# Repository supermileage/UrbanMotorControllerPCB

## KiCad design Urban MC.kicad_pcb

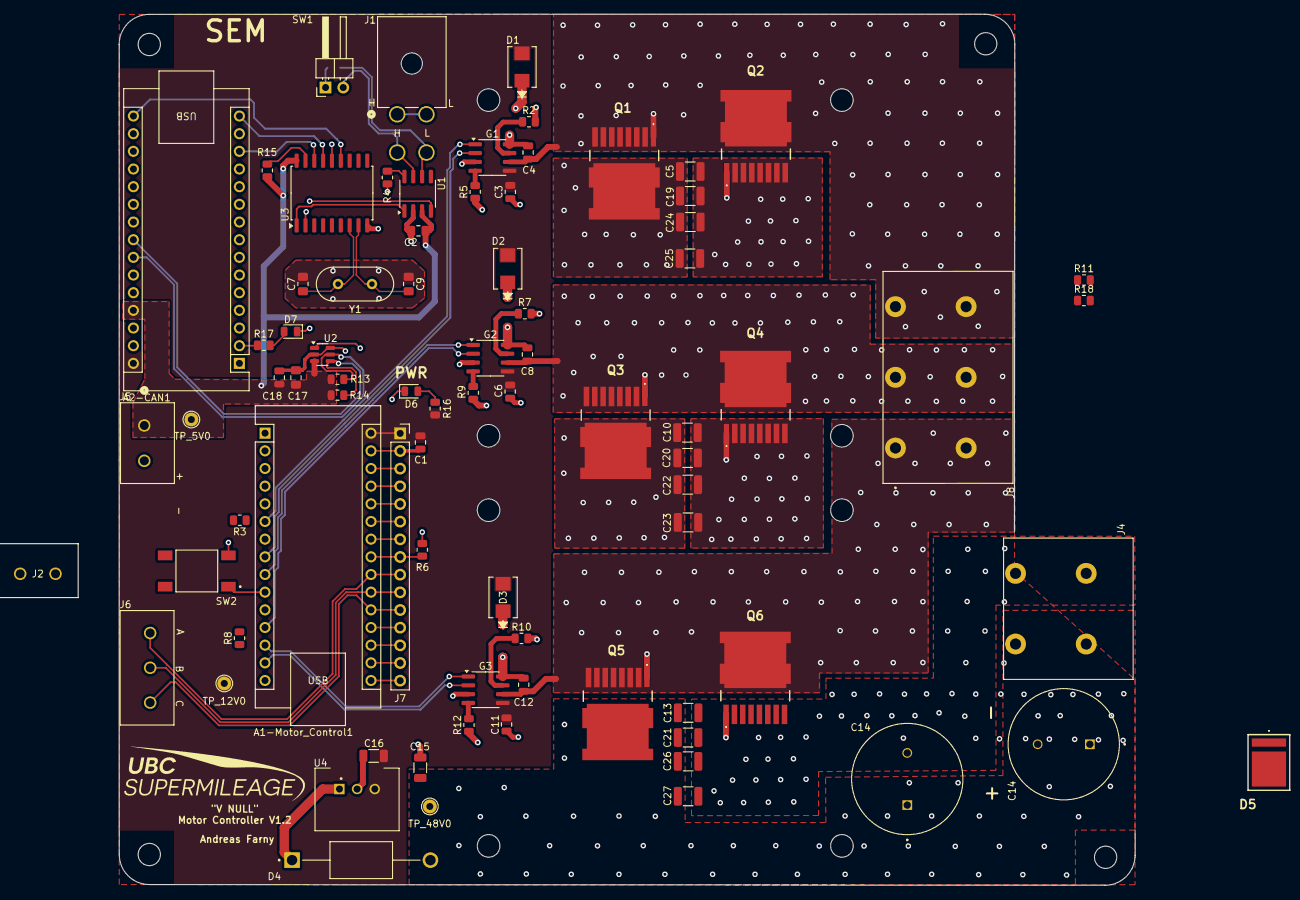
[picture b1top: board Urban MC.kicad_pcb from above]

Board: 6 copper layers, 146.1 x 125.2 mm, 83 parts (1 on the bottom side), 66 nets.

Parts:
A1-Motor_Control1, A2-CAN1: Arduino_Nano_v2.x; Arduino_Nano
C1, C3, C6, C8, C11, C12, C18: 10u; C_0805_2012Metric
C2, C17: 0.1uF; C_0805_2012Metric_Pad1.18x1.45mm_HandSolder
C4: 1u; C_0805_2012Metric
C5, C10, C13: 100 nF; C_1210_3225Metric
C7, C9: 16pF; C_0805_2012Metric_Pad1.18x1.45mm_HandSolder
C14, C14#2: 1m; CAPPRD750W80D1600H2500
C15: 1u; C_1206_3216Metric
C16: 22u; C_1206_3216Metric
C19, C20, C21: 1 uF; C_1210_3225Metric
C22, C24, C26: 4.7 uF; C_1210_3225Metric
C23, C25, C27: 10 uF; C_1210_3225Metric
D1, D2, D3: D; DIODE_DO214AA_MBRS_VIS
D4: D; DIOAD1990W125L900D530
D5: D_TVS; PTVS1058CH
D6, D7: LED; LED_0805_2012Metric
G1, G2, G3: IRS2186; SOIC-8_3.9x4.9mm_P1.27mm
HEATSINK: HEATSINK-518-95AB
HEATSINK#2: HEATSINK-518-95AB
J1: CAN; CONN_5569-04A_MOL
J2: UART_DYNO; CONN_OSTTC022162_OST
J4: VBAT; TE_1-1986660-2
J5: PWR_HALL; CONN_OSTTC022162_OST
J6: HALL_SENSORS; CONN_OSTTC030162_OST
J7: Conn_01x15_Socket; PinSocket_1x15_P2.54mm_Vertical
J8: Conn_02x03_CUSTOM; TE_1986660-3
Q1, Q2, Q3, Q4, Q5, Q6: NTBLS0D8N08XTXG; NVBLS1D1N08H
R1: 120; R_0805_2012Metric
R2, R5, R7, R9, R10, R12: 11Ω; R_0805_2012Metric
R3, R8, R11, R18: 0Ω; R_0805_2012Metric
R4, R15: 10k; R_0805_2012Metric
R6, R13, R14: 10K; R_0805_2012Metric
R16: 4.7k; R_0805_2012Metric
R17: 1.5k; R_0805_2012Metric
SW1: CAN_TERM; PinHeader_1x02_P2.54mm_Horizontal
SW2: SW_MEC_5E; SW_TS04-66-70-BK-160-SMT
TP_5V0, TP_12V0, TP_48V0: TestPoint; TestPoint_THTPad_D2.0mm_Drill1.0mm
U1: MCP2561/2; SOIC-8_3.9x4.9mm_P1.27mm
U2: MCP4725; SOT-23-6
U3: MCP2515-xSO; SOIC-18W_7.5x11.6mm_P1.27mm
U4: CONV_LCW78_12-1.0
Y1: 8MHz; Crystal_HC49-U_Vertical

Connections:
3.3V_OUT: A1-Motor_Control1.17 (3V3), J7.14
5V_OUT: A1-Motor_Control1.27 (+5V), J7.4
+5V: A2-CAN1.27 (+5V), C2.2, C17.1, C18.1, J5.1, R13.1, R14.1, R15.2, TP_5V0.1, U1.3 (VDD), U2.3 (VDD), U3.18 (VDD)
+12V: A1-Motor_Control1.30 (VIN), A2-CAN1.30 (VIN), C1.1, C3.2, C6.2, C11.2, C16.2, D1.2, D2.2, D3.2, G1.5 (VCC), G2.5 (VCC), G3.5 (VCC), J7.1, R16.1, TP_12V0.1, U4.3 (+VOUT)
+48V: C5.1, C10.1, C13.1, C14.1, C15.1, C19.1, C20.1, C21.1, C22.1, C23.1, C24.1, C25.1, C26.1, C27.1, D4.A, D5.2 (A2), J4.1_1 (Pin_1), J4.1_2 (Pin_2), Q1.9 (D), Q1.10 (D_2), Q1.11 (D_3), Q1.12 (D_4), Q3.9 (D), Q3.10 (D_2), Q3.11 (D_3), Q3.12 (D_4), Q5.9 (D), Q5.10 (D_2), Q5.11 (D_3), Q5.12 (D_4), TP_48V0.1
/A4: A2-CAN1.23 (A4), R14.2, U2.4 (SDA)
/A5: A2-CAN1.24 (A5), R13.2, U2.5 (SCL)
/CAN HIGH: J1.3, SW1.2, U1.7 (CANH)
/CAN LOW: J1.4, R1.1, U1.6 (CANL)
/CAN LOW TERM: R1.2, SW1.1
A0: A1-Motor_Control1.19 (A0), J7.12
A5_MC: A1-Motor_Control1.24 (A5), J7.7
A7: A1-Motor_Control1.26 (A7), J7.5
AREF: A1-Motor_Control1.18 (AREF), J7.13
C+: C7.2, U3.7 (OSC2), Y1.1
C-: C9.2, U3.8 (OSC1), Y1.2
CS: A2-CAN1.13 (D10), U3.16 (~CS)
D13: A1-Motor_Control1.16 (D13), J7.15
GND: A1-Motor_Control1.4 (GND), A1-Motor_Control1.29 (GND), A2-CAN1.4 (GND), A2-CAN1.29 (GND), C1.2, C2.1, C3.1, C5.2, C6.1, C7.1, C9.1, C10.2, C11.1, C13.2, C14.2, C15.2, C16.1, C17.2, C18.2, C19.2, C20.2, C21.2, C22.2, C23.2, C24.2, C25.2, C26.2, C27.2, D5.1 (A1), D6.1 (K), D7.1 (K), G1.3 (COM), G2.3 (COM), G3.3 (COM), J1.1, J1.2, J4.2_1 (Pin_3), J4.2_2 (Pin_4), J5.2, J7.2, Q2.2 (S_1), Q2.3 (S_2), Q2.4 (S_3), Q2.5 (S_4), Q2.6 (S_5), Q2.7 (S_6), Q2.8 (S_7), Q4.2 (S_1), Q4.3 (S_2), Q4.4 (S_3), Q4.5 (S_4), Q4.6 (S_5), Q4.7 (S_6), Q4.8 (S_7), Q6.2 (S_1), Q6.3 (S_2), Q6.4 (S_3), Q6.5 (S_4), Q6.6 (S_5), Q6.7 (S_6), Q6.8 (S_7), R4.2, R6.2, SW2.3 (K), U1.2 (VSS), U2.2 (VSS), U2.6 (A0), U3.9 (VSS), U4.2 (GND)
HALL A: A1-Motor_Control1.22 (A3), J6.3, J7.9
HALL B: A1-Motor_Control1.21 (A2), J6.2, J7.10
HALL C: A1-Motor_Control1.20 (A1), J6.1, J7.11
HIN_1: A1-Motor_Control1.2 (D0/RX), G1.1 (HIN)
HIN_2: A1-Motor_Control1.1 (D1/TX), G2.1 (HIN)
HIN_3: A1-Motor_Control1.12 (D9), G3.1 (HIN)
LIN_1: A1-Motor_Control1.9 (D6), G1.2 (LIN)
LIN_2: A1-Motor_Control1.6 (D3), G2.2 (LIN)
LIN_3: A1-Motor_Control1.25 (A6), G3.2 (LIN), J7.6
unnamed: A1-Motor_Control1.5 (D2), R3.1
unnamed: A1-Motor_Control1.10 (D7), SW2.1
unnamed: A1-Motor_Control1.13 (D10), R8.1
unnamed: A2-CAN1.2 (D0/RX), R17.1
unnamed: D6.2 (A), R16.2
unnamed: D7.2 (A), R17.2
unnamed: G1.7 (HO), R2.1
unnamed: G1.4 (LO), R5.1
unnamed: C4.2, D1.1, G1.8 (VB)
unnamed: G2.7 (HO), R7.1
unnamed: G2.4 (LO), R9.1
unnamed: C8.2, D2.1, G2.8 (VB)
unnamed: G3.7 (HO), R10.1
unnamed: G3.4 (LO), R12.1
unnamed: C12.2, D3.1, G3.8 (VB)
unnamed: Q1.1 (G), R2.2
unnamed: Q2.1 (G), R5.2
unnamed: Q3.1 (G), R7.2
unnamed: Q4.1 (G), R9.2
unnamed: Q5.1 (G), R10.2
unnamed: Q6.1 (G), R12.2
unnamed: R4.1, U1.8 (Rs)
unnamed: R11.1, U3.2 (RXCAN)
unnamed: R18.1, U3.1 (TXCAN)
unnamed: R15.1, U3.17 (~RESET)
unnamed: D4.C, U4.1 (+VIN)
PHASE 1 OUTPUT: C4.1, G1.6 (VS), J8.3_1, J8.3_2, Q1.2 (S_1), Q1.3 (S_2), Q1.4 (S_3), Q1.5 (S_4), Q1.6 (S_5), Q1.7 (S_6), Q1.8 (S_7), Q2.9 (D), Q2.10 (D_2), Q2.11 (D_3), Q2.12 (D_4)
PHASE 2 OUTPUT: C8.1, G2.6 (VS), J8.2_1, J8.2_2, Q3.2 (S_1), Q3.3 (S_2), Q3.4 (S_3), Q3.5 (S_4), Q3.6 (S_5), Q3.7 (S_6), Q3.8 (S_7), Q4.9 (D), Q4.10 (D_2), Q4.11 (D_3), Q4.12 (D_4)
PHASE 3 OUTPUT: C12.1, G3.6 (VS), J8.1_1, J8.1_2, Q5.2 (S_1), Q5.3 (S_2), Q5.4 (S_3), Q5.5 (S_4), Q5.6 (S_5), Q5.7 (S_6), Q5.8 (S_7), Q6.9 (D), Q6.10 (D_2), Q6.11 (D_3), Q6.12 (D_4)
RESET: A1-Motor_Control1.28 (~RESET), J7.3
RXCAN: R8.2, R11.2, U1.4 (RXD)
SCK: A2-CAN1.16 (D13), U3.13 (SCK)
SI: A2-CAN1.14 (D11), U3.14 (SI)
SO: A2-CAN1.15 (D12), U3.15 (SO)
THROTTLE: A1-Motor_Control1.23 (A4), J7.8, R6.1, U2.1 (VOUT)
TXCAN: R3.2, R18.2, U1.1 (TXD)
UART_DYNO_RX: A1-Motor_Control1.7 (D4), J2.1
UART_DYNO_TX: A1-Motor_Control1.8 (D5), J2.2

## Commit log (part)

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2024-10-12 added footprints and datasheets
2024-10-19 updated LCW footprint to match size
2024-10-26 Updated footprint for schematic
2024-11-02 error fixes
2024-11-02 why not working
2024-11-02 pls work
2024-11-02 test
2024-11-02 footprint
2024-11-16 first push
2024-11-16 custom footprint for MOSFETs
2024-11-16 added custom footprints
2024-11-17 updated schematic
2024-11-23 Added diodes
2024-11-30 Updated mosfet symbol
2024-11-30 Updated layout
2024-11-30 mosfets
2024-12-02 updated schematic and layout
2025-01-04 Updated Connectors from Metal Screw to Screw Terminal
2025-01-04 MOSFET section draft
2025-01-06 MOSFETsection with some changes
2025-01-11 mosfet
2025-01-11 ready for mosfet feedback
2025-01-11 symbol changes and filled zone solution, still looking for more feedback
2025-01-18 duplicated mosfet section with connected filled zones
2025-01-19 organized fet arduino circuit components
2025-01-22 CAN circuit and voltage regulator first draft, mounting holes
2025-01-22 small trace edits
2025-01-27 in the middle of layout changes- expanding right side and drawing gate driver traces
2025-01-30 filledempty space with filled zones, grounded components
2025-02-01 Duplicated filled zones, finished CAN section, organized component labels
2025-02-01 vias
2025-02-01 connector labels
2025-02-01 final edits: power 12V islands, adjusting vias to pass DRC
2025-02-02 post design review
2025-02-05 grounding components with vias instead of long traces, 5V filled zone and MCP4725 complementary components
2025-02-06 Phase output net names, keepouts on mounting holes, logo, other small fixes
2025-02-07 5V filled zone edits
2025-02-08 all datasheets except CAN TERM and crystal
2025-02-08 making room to flash to A2
2025-02-08 heatsinks, ready for design review
2025-02-09 small changed from design review: hallpower is an OUTPUT
2025-02-10 Test points, fixed footprint warnings, logo, and fabrication files
2025-02-10 Gerbers
2025-02-11 complete output files
2025-02-11 Silkscreen edits, redone Gerbers
2025-02-11 Gerber and silkscreen edits
2025-02-11 zipped Gerber
2025-02-11 more silkscreen edits
2025-03-07 V1.1
2025-03-07 lager pads for J3, J4
2025-03-08 slightly smaller pads for J3, J4 to pass DRC
2025-03-09 CAN connector changes
2025-03-09 V1.1 ORDERED
2025-09-07 schematic cleanup
2025-09-26 Schematic cleanup and start of big layout changes
2025-10-06 Layout almost complete, just need to add vias
2025-10-07 peppered vias
2025-10-13 design review changes in progress
2025-10-17 Design Review Changes (WIP)
2025-10-22 all post-design review changes except vias
2025-10-24 Final Review before order
2025-11-01 V1.2 ORDERED VERSION
2025-11-16 D1-3 BOM change
2026-01-06 V1.2 STEP file 1
